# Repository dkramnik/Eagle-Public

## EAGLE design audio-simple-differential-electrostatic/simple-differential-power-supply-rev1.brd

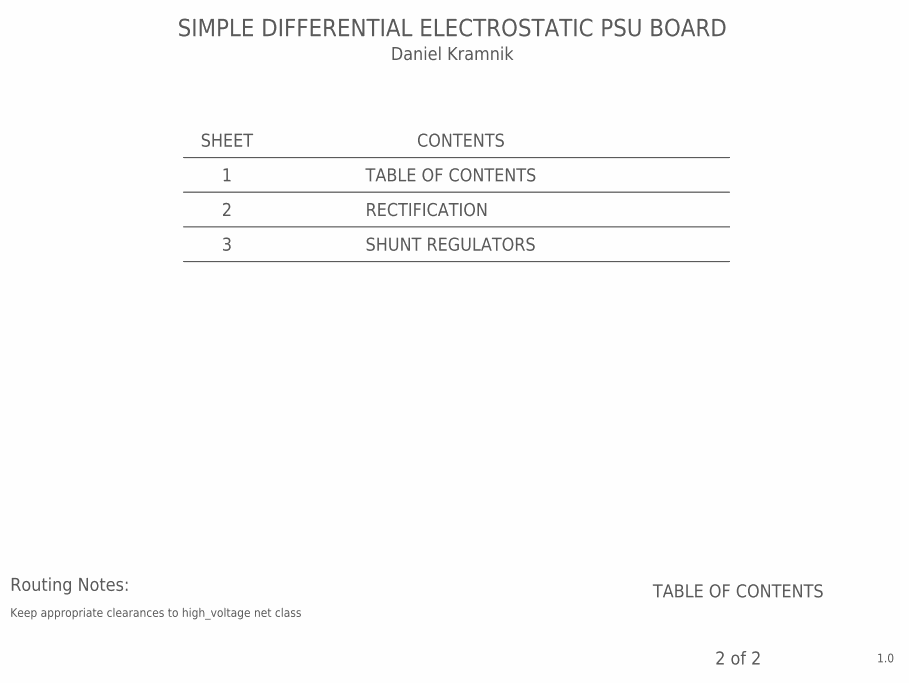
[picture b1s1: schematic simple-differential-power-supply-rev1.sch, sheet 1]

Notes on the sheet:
TABLE OF CONTENTS
1.0
2 of 2
SIMPLE DIFFERENTIAL ELECTROSTATIC PSU BOARD
SHEET
CONTENTS
Daniel Kramnik
RECTIFICATION
SHUNT REGULATORS
Routing Notes:
Keep appropriate clearances to high_voltage net class

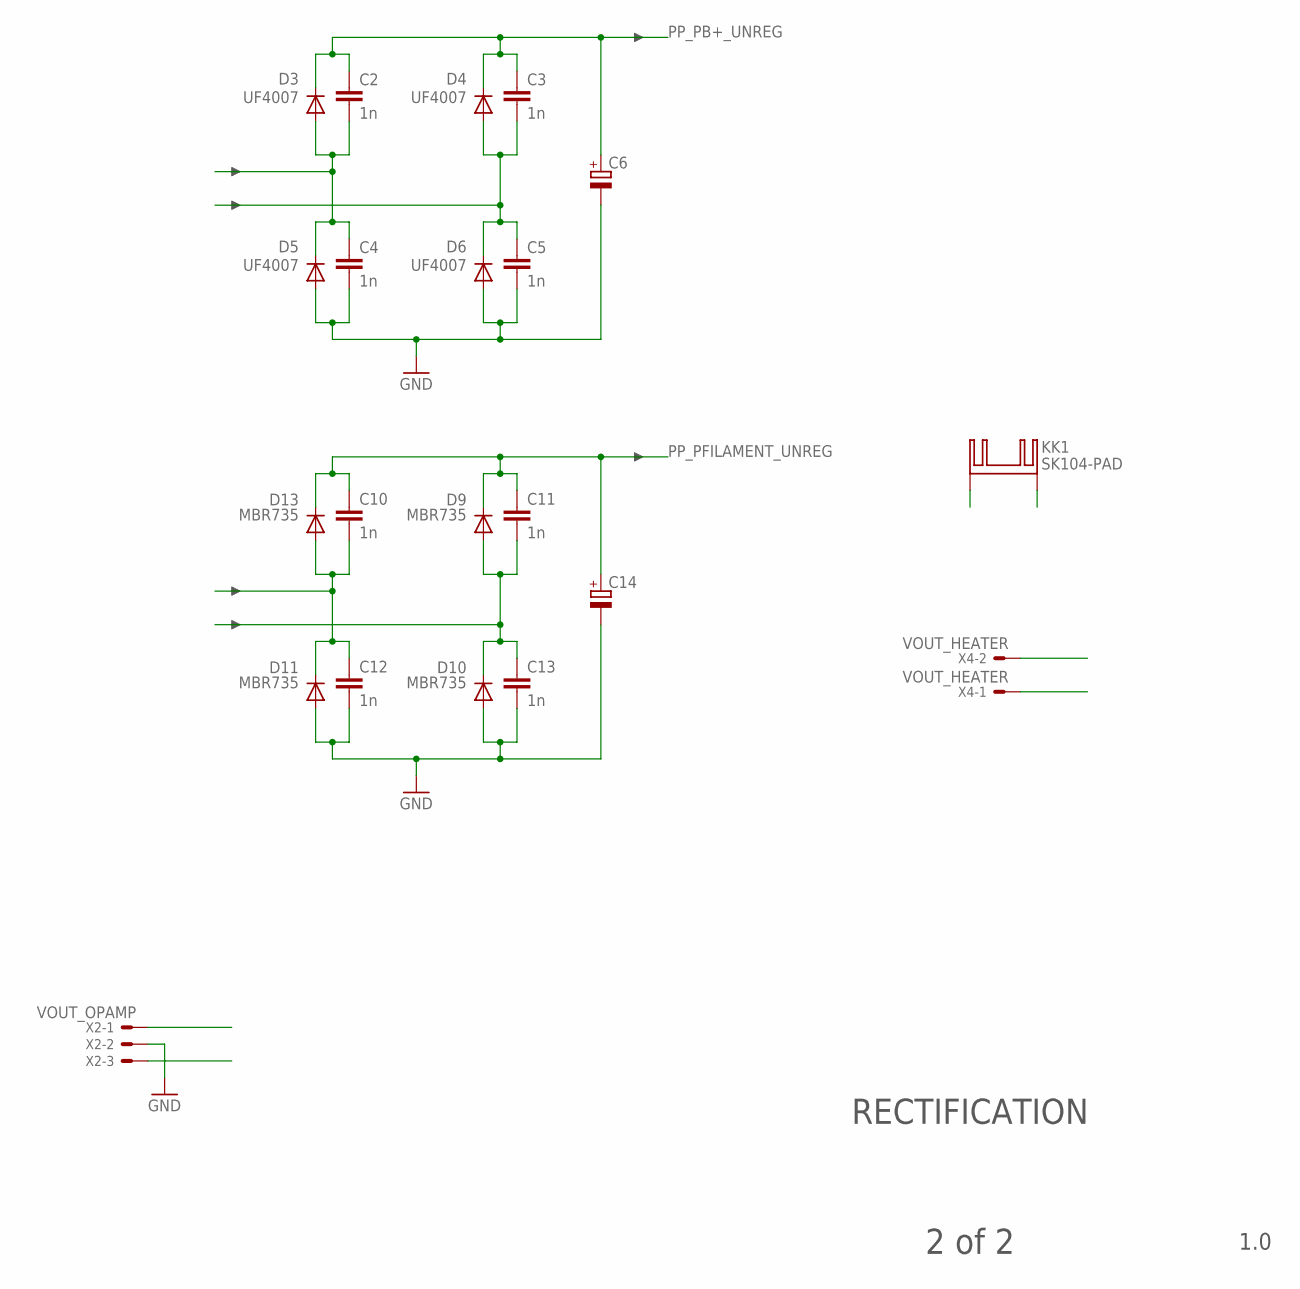
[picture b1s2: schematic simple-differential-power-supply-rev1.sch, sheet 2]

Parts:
C2, C3, C4, C5, C10, C11, C12, C13: 1n; C225-087X268
C6, C14: CPOL-EUE10-25; EB25D
D3, D4, D5, D6: UF4007; DO41-10
D9, D10, D11, D13: MBR735; TO220ACS
KK1: SK104-PAD
X2: VOUT_OPAMP; KK-156-3
X4: VOUT_HEATER; KK-156-2

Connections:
GND: C4.2, C5.2, C6.-, C12.2, C13.2, C14.-, D5.A, D6.A, D10.A, D11.A, X2.2; also elsewhere on the board
unnamed: C11.2, C13.1, D9.A, D10.C
unnamed: C10.2, C12.1, D11.C, D13.A
unnamed: C3.2, C5.1, D4.A, D6.C
unnamed: C2.2, C4.1, D3.A, D5.C
PP_PB+_UNREG: C2.1, C3.1, C6.+, D3.C, D4.C; also elsewhere on the board
PP_PFILAMENT_UNREG: C10.1, C11.1, C14.+, D9.C, D13.C

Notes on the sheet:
RECTIFICATION
1.0
2 of 2

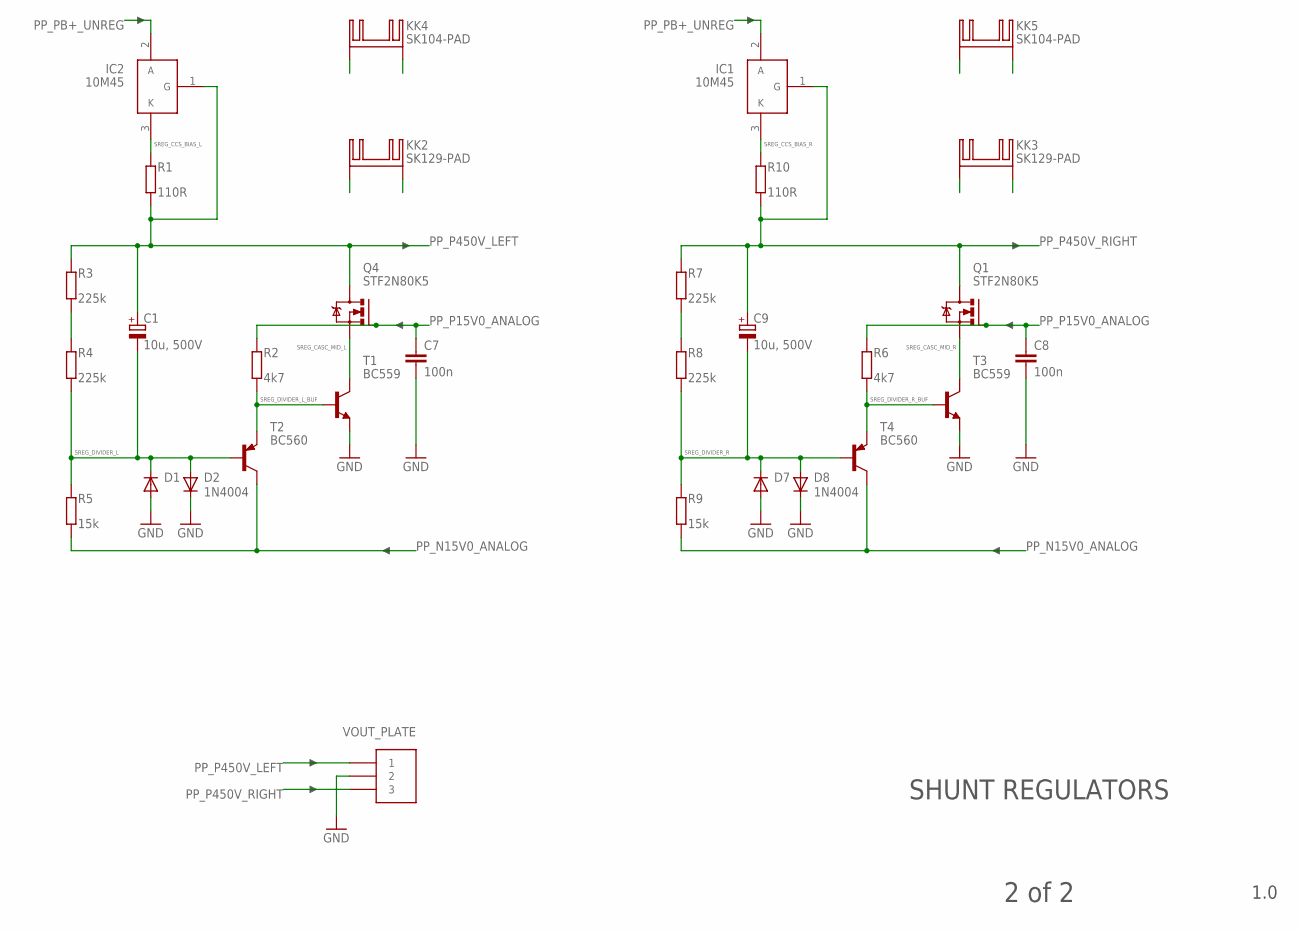
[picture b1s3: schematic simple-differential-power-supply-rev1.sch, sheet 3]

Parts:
C1, C9: 10u, 500V; EB25D
C7, C8: 100n; C050-025X075
D1, D2, D7, D8: 1N4004; DO41-10
IC1, IC2: 10M45; TO220V
J2: VOUT_PLATE; CONN_MOLEX_3PIN_MINI-FIT_JR
KK2, KK3: SK129-PAD; SK129
KK4, KK5: SK104-PAD
Q1, Q4: STF2N80K5; TO220BV
R1, R10: 110R; 0309/10
R2, R6: 4k7; 0309/10
R3, R4, R7, R8: 225k; 0309/10
R5, R9: 15k; 0309/10
T1, T3: BC559; TO92-EBC
T2, T4: BC560; TO92-EBC

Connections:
GND: C7.2, C8.2, D1.A, D2.C, D7.A, D8.C, J2.2, T1.E, T3.E; also elsewhere on the board
unnamed: R3.1, R4.2
unnamed: R7.1, R8.2
PP_N15V0_ANALOG: R5.1, R9.1, T2.C, T4.C
PP_P15V0_ANALOG: C7.1, C8.1, Q1.G, Q4.G, R2.2, R6.2
PP_P450V_LEFT: C1.+, IC2.1 (G), J2.1, Q4.D, R1.1, R3.2
PP_P450V_RIGHT: C9.+, IC1.1 (G), J2.3, Q1.D, R7.2, R10.1
PP_PB+_UNREG: IC1.2 (A), IC2.2 (A); also elsewhere on the board
SREG_CASC_MID_L: Q4.S, T1.C
SREG_CASC_MID_R: Q1.S, T3.C
SREG_CCS_BIAS_L: IC2.3 (K), R1.2
SREG_CCS_BIAS_R: IC1.3 (K), R10.2
SREG_DIVIDER_L: C1.-, D1.C, D2.A, R4.1, R5.2, T2.B
SREG_DIVIDER_L_BUF: R2.1, T1.B, T2.E
SREG_DIVIDER_R: C9.-, D7.C, D8.A, R8.1, R9.2, T4.B
SREG_DIVIDER_R_BUF: R6.1, T3.B, T4.E

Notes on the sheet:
SHUNT REGULATORS
1.0
2 of 2

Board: 2 copper layers, 52 parts (0 on the bottom side), 21 nets, no tracks yet.

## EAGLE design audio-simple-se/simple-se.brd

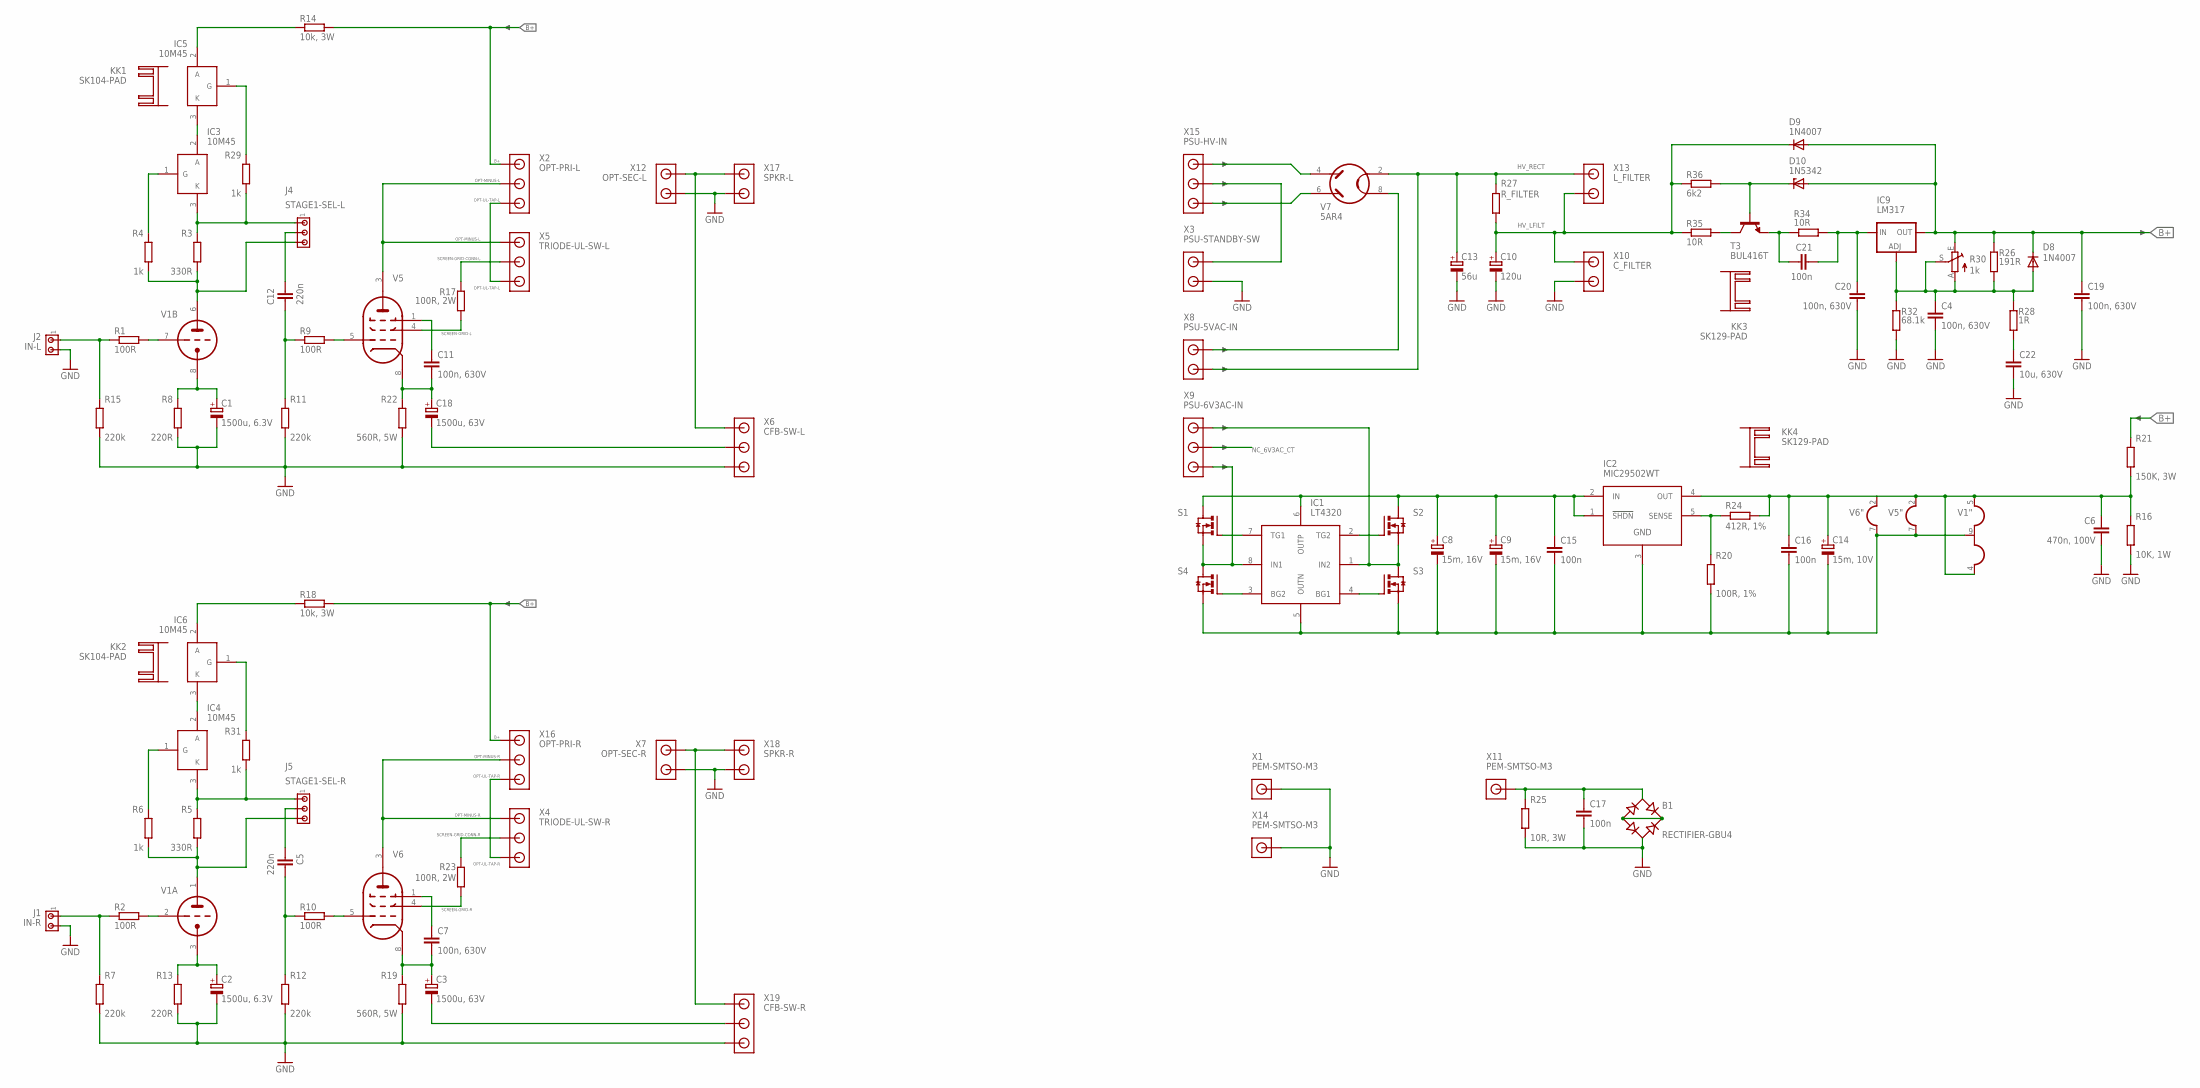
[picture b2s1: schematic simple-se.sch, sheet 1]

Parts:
B1: RECTIFIER-GBU4; GBU4
C1, C2: 1500u, 6.3V; E5-10,5
C3, C18: 1500u, 63V; E5-13
C4, C7, C11, C19, C20: 100n, 630V; C150-072X183
C5, C12: 220n; C275-113X316
C6: 470n, 100V; C075-063X106
C8, C9: 15m, 16V; E7,5-18
C10: 120u; EB30D
C13: 56u; EB22,5D
C14: 15m, 10V; E7,5-18
C15, C16: 100n; C050-055X075
C17: 100n; C102-043X133
C21: 100n; C150-072X183
C22: 10u, 630V; C150-072X183
D8, D9: 1N4007; DO41-10
D10: 1N5342; DO35Z10
IC1: LT4320; DIL08
IC2: MIC29502WT; TO220-5
IC3, IC4, IC5, IC6: 10M45; TO220V
IC9: LM317; 317TS
J1: IN-R; 1X2MTA
J2: IN-L; 1X2MTA
J4: STAGE1-SEL-L; 1X3MTA
J5: STAGE1-SEL-R; 1X3MTA
KK1, KK2: SK104-PAD
KK3, KK4: SK129-PAD; SK129
R1, R2, R9, R10: 100R; 0309/12
R3, R5: 330R; 0309/12
R4, R6, R29, R31: 1k; 0309/12
R7, R11, R12, R15: 220k; 0309/12
R8, R13: 220R; 0309/12
R14, R18: 10k, 3W; 0617/22
R16: 10K, 1W; 0309/12
R17, R23: 100R, 2W; 0411/12
R19, R22: 560R, 5W; 0922/22
R20: 100R, 1%; 0309/12
R21: 150K, 3W; 0617/22
R24: 412R, 1%; 0309/12
R25: 10R, 3W; 0617/17
R26: 191R; 0309/12
R27: R_FILTER; 0922/22
R28: 1R; 0309/12
R30: 1k; S64W
R32: 68.1k; 0309/12
R34, R35: 10R; 0309/12
R36: 6k2; 0309/12
S1, S2, S3, S4: MOSFET-N_DPAK; DPAK
T3: BUL416T; TO220V
V1: 12AT7-P; NOVAL
V5, V6: EL34-P; OKTAL
V7: 5AR4; OKTAL
X1, X11, X14: PEM-SMTSO-M3; SMTSO-M3
X2: OPT-PRI-L; MOLEX-SPOX-5281-3POS
X3: PSU-STANDBY-SW; MOLEX-SPOX-5281-2POS
X4: TRIODE-UL-SW-R; MOLEX-SPOX-5281-3POS
X5: TRIODE-UL-SW-L; MOLEX-SPOX-5281-3POS
X6: CFB-SW-L; MOLEX-SPOX-5281-3POS
X7: OPT-SEC-R; MOLEX-SPOX-5281-2POS
X8: PSU-5VAC-IN; MOLEX-SPOX-5281-2POS
X9: PSU-6V3AC-IN; MOLEX-SPOX-5281-3POS
X10: C_FILTER; MOLEX-SPOX-5281-2POS
X12: OPT-SEC-L; MOLEX-SPOX-5281-2POS
X13: L_FILTER; MOLEX-SPOX-5281-2POS
X15: PSU-HV-IN; MOLEX-SPOX-5281-3POS
X16: OPT-PRI-R; MOLEX-SPOX-5281-3POS
X17: SPKR-L; MOLEX-SPOX-5281-2POS
X18: SPKR-R; MOLEX-SPOX-5281-2POS
X19: CFB-SW-R; MOLEX-SPOX-5281-3POS

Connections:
B+: C19.1, D8.C, D9.A, D10.A, IC9.2 (OUT), R14.1, R18.1, R21.2, R26.2, R30.E, X2.P$1 (1), X16.P$1 (1)
GND: B1.AC2, C1.-, C2.-, C4.2, C6.2, C10.-, C13.-, C17.2, C19.2, C20.2, C22.2, J1.2, J2.2, R7.1, R8.1, R11.1, R12.1, R13.1, R15.1, R16.1, R19.1, R22.1, R25.1, R32.1, X1.P$1, X3.P$2 (2), X6.P$3 (3), X7.P$2 (2), X10.P$2 (2), X12.P$2 (2), X14.P$1, X17.P$2 (2), X18.P$2 (2), X19.P$3 (3)
HV_LFILT: C10.+, D9.C, R27.1, R35.2, R36.2, X10.P$1 (1), X13.P$2 (2)
HV_RECT: C13.+, R27.2, V7.2 (H1), X8.P$2 (2), X13.P$1 (1)
unnamed: R1.1, V1.7 (TG)
unnamed: J4.3, R3.1, R4.1, V1.6 (TA)
unnamed: R2.1, V1.2 (TG)
unnamed: J5.3, R5.1, R6.1, V1.1 (TA)
unnamed: IC4.3 (K), J5.1, R5.2, R31.1
unnamed: IC4.1 (G), R6.2
unnamed: IC3.3 (K), J4.1, R3.2, R29.1
unnamed: IC3.1 (G), R4.2
unnamed: J1.1, R2.2, R7.2
unnamed: J2.1, R1.2, R15.2
unnamed: R9.1, V5.5 (PG)
unnamed: B1.+, B1.-
unnamed: C5.2, R10.2, R12.2
unnamed: C12.1, R9.2, R11.2
unnamed: C1.+, R8.2, V1.8 (TK)
unnamed: C2.+, R13.2, V1.3 (TK)
unnamed: IC6.2 (A), R18.2
unnamed: IC3.2 (A), IC5.3 (K)
unnamed: C18.-, X6.P$2 (2)
unnamed: R10.1, V6.5 (PG)
unnamed: B1.AC1, C17.1, R25.2, X11.P$1
unnamed: X3.P$1 (1), X15.P$2 (2)
unnamed: X6.P$1 (1), X12.P$1 (1), X17.P$1 (1)
unnamed: R35.1, T3.2 (C)
unnamed: C4.1, D8.A, IC9.1 (ADJ), R26.1, R28.2, R30.A, R30.S, R32.2
unnamed: V7.4 (A1), X15.P$1 (1)
unnamed: IC1.7 (TG1), S1.1 (G)
unnamed: C21.1, R34.2, T3.3 (E)
unnamed: C20.1, C21.2, IC9.3 (IN), R34.1
unnamed: C11.2, C18.+, R22.2, V5.8 (PK)
unnamed: C7.1, V6.1 (PBG)
unnamed: C3.+, C7.2, R19.2, V6.8 (PK)
unnamed: V7.6 (A2), X15.P$3 (3)
unnamed: IC1.8 (IN1), S1.3 (S), S4.4 (D), X9.P$3 (3)
unnamed: V7.8 (H2), X8.P$1 (1)
unnamed: X7.P$1 (1), X18.P$1 (1), X19.P$1 (1)
unnamed: C22.1, R28.1
unnamed: C11.1, V5.1 (PBG)
unnamed: C8.+, C9.+, C15.1, IC1.6 (OUTP), IC2.1 (!SHDN), IC2.2 (IN), S1.4 (D), S2.4 (D)
unnamed: IC1.3 (BG2), S4.1 (G)
unnamed: IC1.2 (TG2), S2.1 (G)
unnamed: IC1.1 (IN2), S2.3 (S), S3.4 (D), X9.P$1 (1)
unnamed: IC1.4 (BG1), S3.1 (G)
unnamed: C8.-, C9.-, C14.-, C15.2, C16.2, IC1.5 (OUTN), IC2.3 (GND), R20.1, S3.3 (S), S4.3 (S), V1.9 (H2), V5.7 (H2), V6.7 (H2)
unnamed: C6.1, C14.+, C16.1, IC2.4 (OUT), R16.2, R21.1, R24.1, V1.4 (H1), V1.5 (H3), V5.2 (H1), V6.2 (H1)
unnamed: D10.C, R36.1, T3.1 (B)
unnamed: IC2.5 (SENSE), R20.2, R24.2
unnamed: IC5.1 (G), R29.2
unnamed: IC5.2 (A), R14.2
unnamed: C12.2, J4.2
unnamed: IC4.2 (A), IC6.3 (K)
unnamed: IC6.1 (G), R31.2
unnamed: C5.1, J5.2
NC_6V3AC_CT: X9.P$2 (2)
OPT-MINUS-L: V5.3 (PA), X2.P$2 (2), X5.P$1 (1)
OPT-MINUS-R: V6.3 (PA), X4.P$1 (1), X16.P$2 (2)
OPT-UL-TAP-L: X2.P$3 (3), X5.P$3 (3)
OPT-UL-TAP-R: X4.P$3 (3), X16.P$3 (3)
SCREEN-GRID-CONN-L: R17.1, X5.P$2 (2)
SCREEN-GRID-CONN-R: R23.1, X4.P$2 (2)
SCREEN-GRID-L: R17.2, V5.4 (PSG)
SCREEN-GRID-R: R23.2, V6.4 (PSG)

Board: 2 copper layers, 104 parts (9 on the bottom side), 65 nets, no tracks yet.

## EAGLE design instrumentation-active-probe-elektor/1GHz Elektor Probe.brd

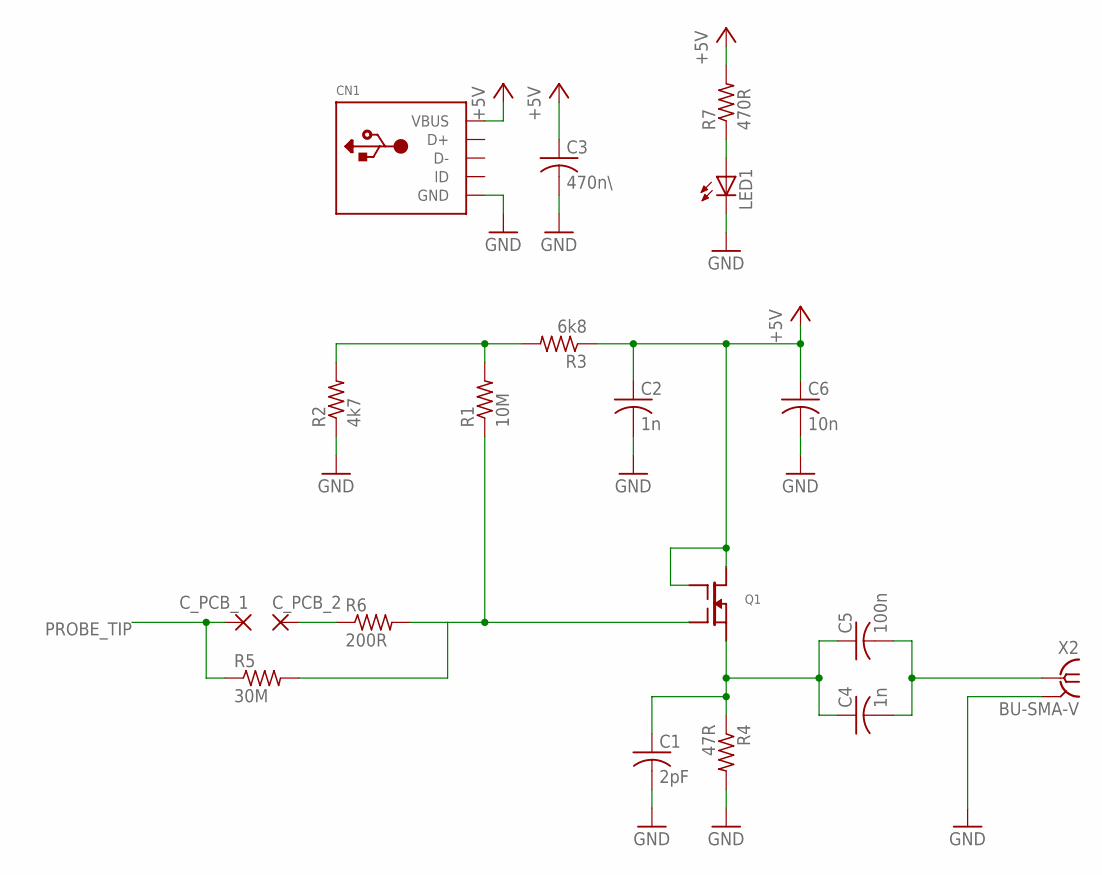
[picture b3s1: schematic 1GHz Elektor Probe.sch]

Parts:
C1: 2pF; C0805
C2, C4: 1n; C0805
C3: 470n\; C0805
C5: 100n; C0805
C6: 10n; C0805
CN1: USBMINIB; USB-MINIB
C_PCB_1, C_PCB_2: SMD5; SMD2,54-5,08
LED1: LED3MM
Q1: BF998; SOT143B
R1: 10M; R0805
R2: 4k7; R0805
R3: 6k8; R0805
R4: 47R; R0805
R5: 30M; R0805
R6: 200R; R0805
R7: 470R; R0805
X2: BU-SMA-V

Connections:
+5V: C2.1, C3.1, C6.1, CN1.VBUS, Q1.2 (D), Q1.3 (G2), R3.1, R7.2
GND: C1.2, C2.2, C3.2, C6.2, CN1.GND, LED1.K (C), R2.1, R4.2, X2.2 (GND), X2.3 (GND), X2.4 (GND), X2.5 (GND)
unnamed: C1.1, C4.1, C5.1, Q1.1 (S), R4.1
unnamed: C_PCB_2.1, R6.1
unnamed: R1.2, R2.2, R3.2
unnamed: LED1.A, R7.1
unnamed: C4.2, C5.2, X2.1
unnamed: Q1.4 (G1), R1.1, R5.2, R6.2
PROBE_TIP: C_PCB_1.1, R5.1

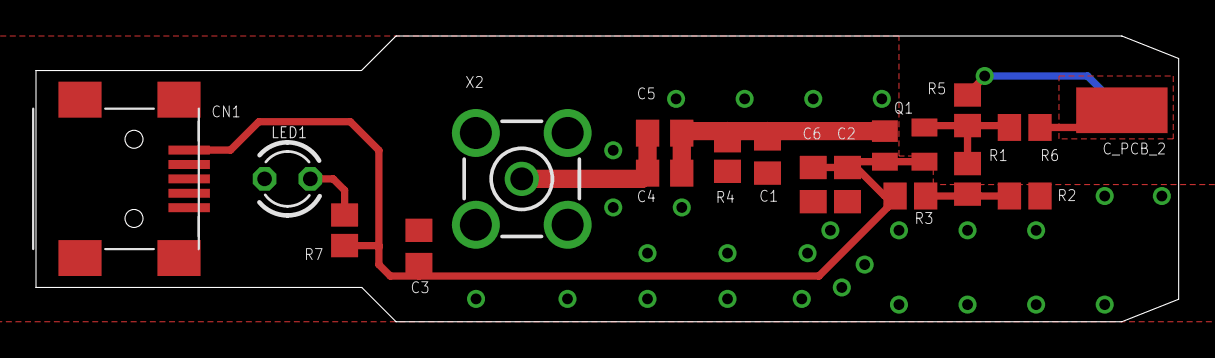
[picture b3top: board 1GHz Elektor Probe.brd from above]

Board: 2 copper layers, 63.5 x 15.9 mm, 19 parts (1 on the bottom side), 9 nets.

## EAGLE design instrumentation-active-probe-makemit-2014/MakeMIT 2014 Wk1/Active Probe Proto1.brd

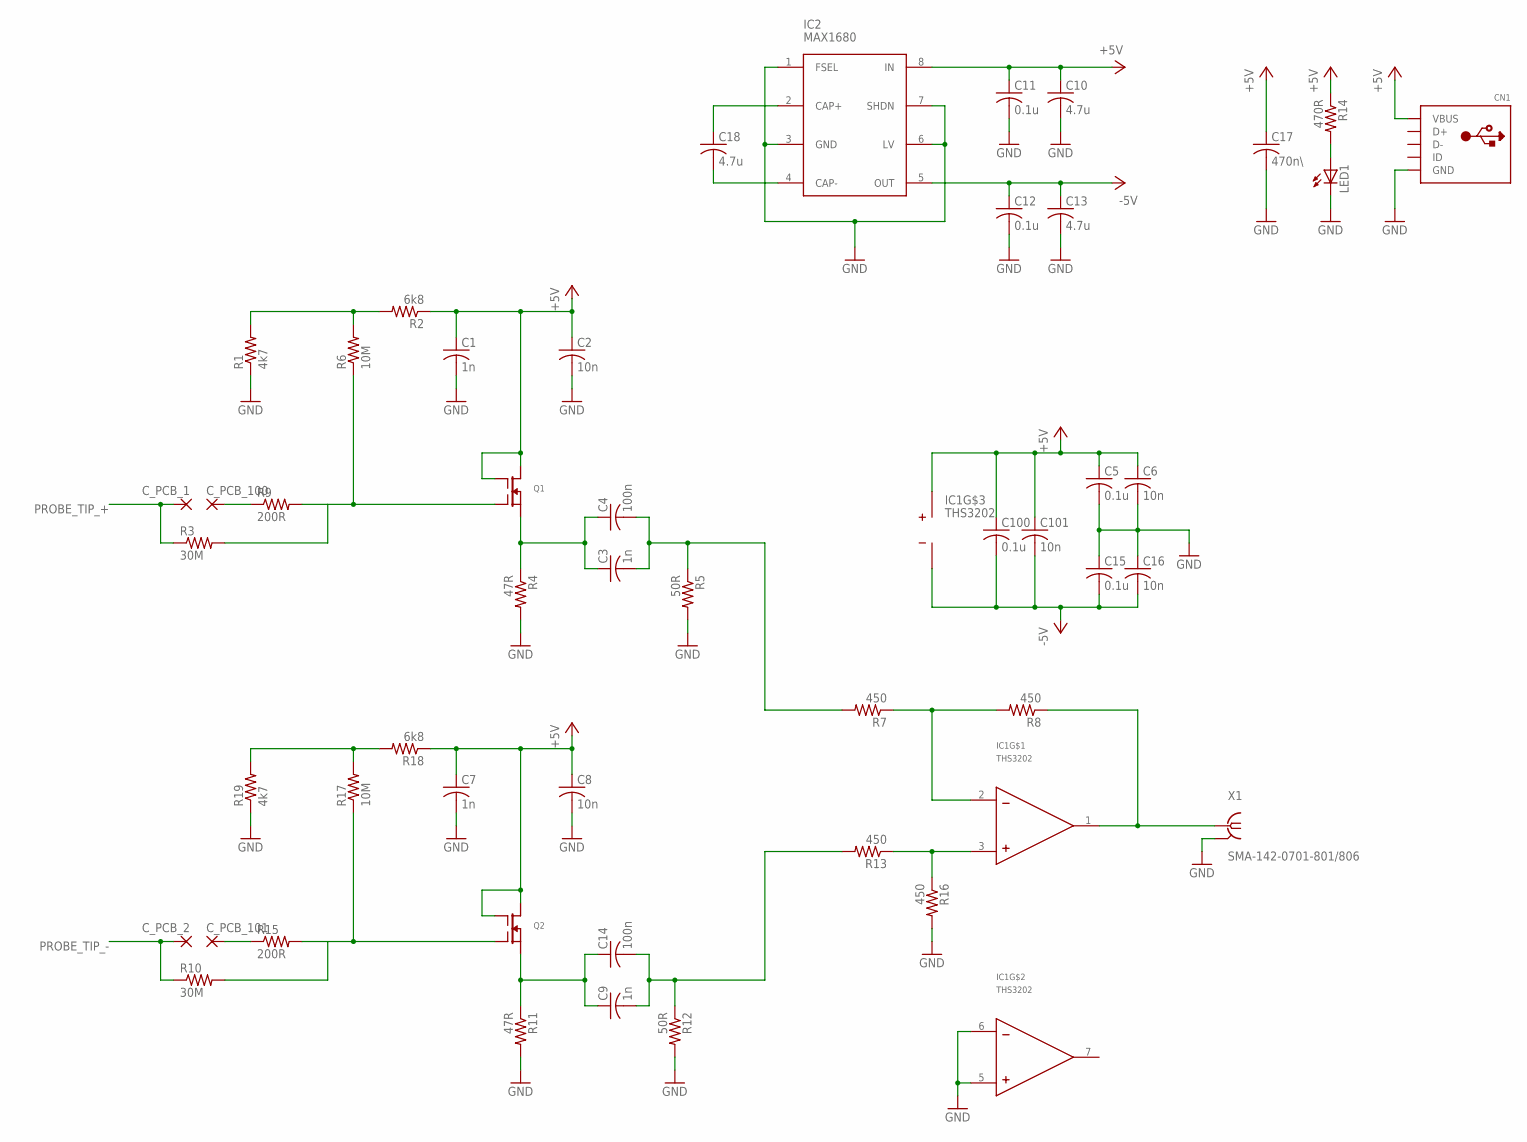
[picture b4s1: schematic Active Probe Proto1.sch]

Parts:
C1, C3, C7, C9: 1n; C0805
C2, C6, C8, C16, C101: 10n; C0805
C4, C14: 100n; C0805
C5, C11, C12, C15, C100: 0.1u; C0805
C10, C13, C18: 4.7u; C0805
C17: 470n\; C0805
CN1: USBMINIB; USB-MINIB
C_PCB_1, C_PCB_2, C_PCB_100, C_PCB_101: SMD5; SMD2,54-5,08
IC1: THS3202; SOIC8
IC2: MAX1680; SO8
LED1: LED3MM
Q1, Q2: BF998; SOT143B
R1, R19: 4k7; R0805
R2, R18: 6k8; R0805
R3, R10: 30M; R0805
R4, R11: 47R; R0805
R5, R12: 50R; R0805
R6, R17: 10M; R0805
R7, R8, R13, R16: 450; R0805
R9, R15: 200R; R0805
R14: 470R; R0805
X1: SMA-142-0701-801/806; J502-ND-142-0701-801/806

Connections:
+5V: C1.1, C2.1, C5.1, C6.1, C7.1, C8.1, C10.1, C11.1, C17.1, C100.1, C101.1, CN1.VBUS, IC1.8 (VCC), IC2.8 (IN), Q1.2 (D), Q1.3 (G2), Q2.2 (D), Q2.3 (G2), R2.1, R14.1, R18.1
-5V: C12.1, C13.1, C15.2, C16.2, C100.2, C101.2, IC1.4 (GND), IC2.5 (OUT)
GND: C1.2, C2.2, C5.2, C6.2, C7.2, C8.2, C10.2, C11.2, C12.2, C13.2, C15.1, C16.1, C17.2, CN1.GND, IC1.5 (IN+), IC1.6 (IN-), IC2.1 (FSEL), IC2.3 (GND), IC2.6 (LV), IC2.7 (SHDN), LED1.K (C), R1.1, R4.2, R5.2, R11.2, R12.2, R16.2, R19.1, X1.G@1 (GND), X1.G@2 (GND), X1.G@3 (GND), X1.G@4 (GND)
unnamed: R17.2, R18.2, R19.2
unnamed: C3.1, C4.1, Q1.1 (S), R4.1
unnamed: R1.2, R2.2, R6.2
unnamed: C_PCB_100.1, R9.1
unnamed: C3.2, C4.2, R5.1, R7.2
unnamed: Q1.4 (G1), R3.2, R6.1, R9.2
unnamed: C9.2, C14.2, R12.1, R13.2
unnamed: Q2.4 (G1), R10.2, R15.2, R17.1
unnamed: C9.1, C14.1, Q2.1 (S), R11.1
unnamed: C_PCB_101.1, R15.1
unnamed: LED1.A, R14.2
unnamed: IC1.1 (OUT), R8.1, X1.1
unnamed: C18.2, IC2.4 (CAP-)
unnamed: C18.1, IC2.2 (CAP+)
unnamed: IC1.3 (IN+), R13.1, R16.1
unnamed: IC1.2 (IN-), R7.1, R8.2
PROBE_TIP_+: C_PCB_1.1, R3.1
PROBE_TIP_-: C_PCB_2.1, R10.1

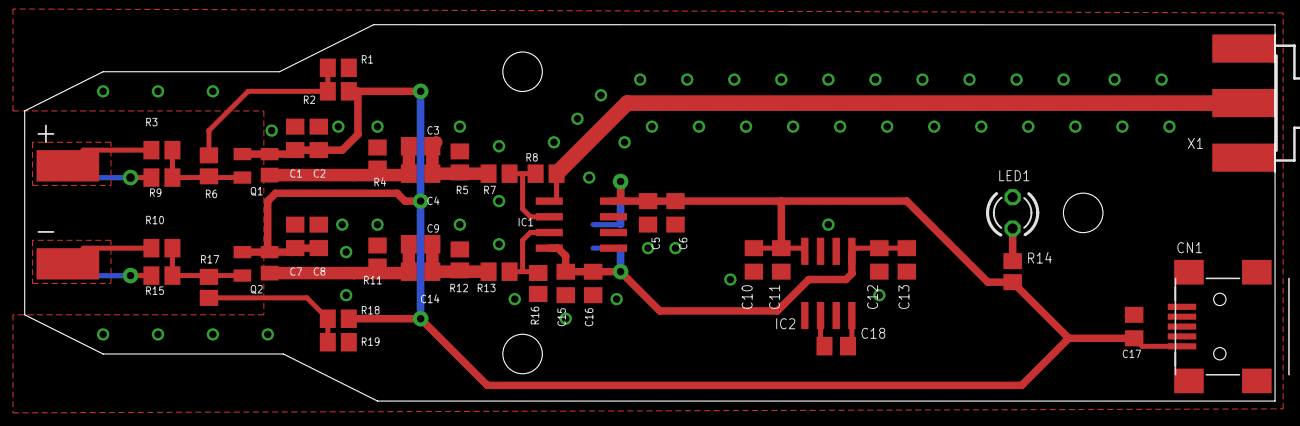
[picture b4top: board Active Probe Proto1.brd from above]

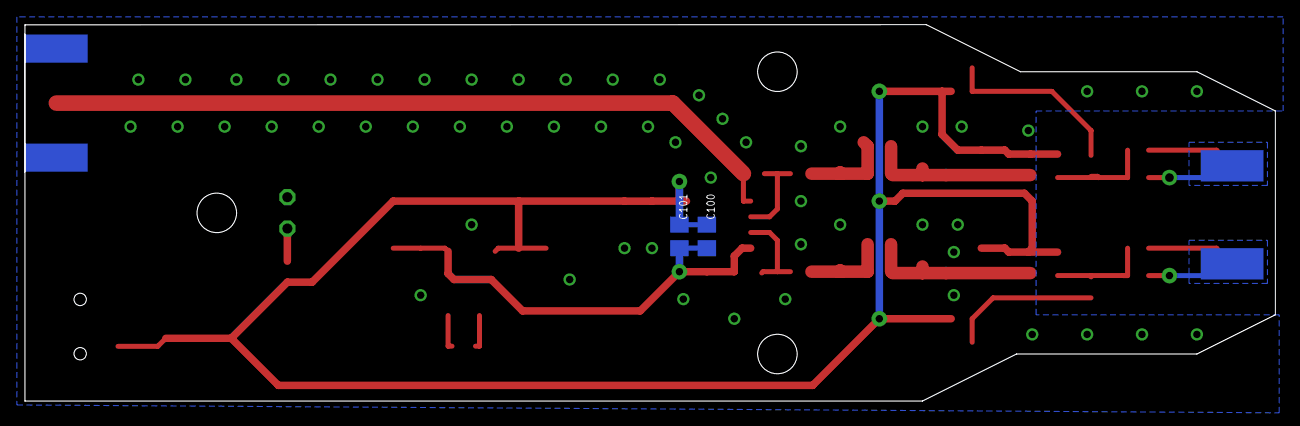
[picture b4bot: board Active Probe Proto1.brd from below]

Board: 2 copper layers, 101.3 x 30.5 mm, 50 parts (4 on the bottom side), 21 nets.

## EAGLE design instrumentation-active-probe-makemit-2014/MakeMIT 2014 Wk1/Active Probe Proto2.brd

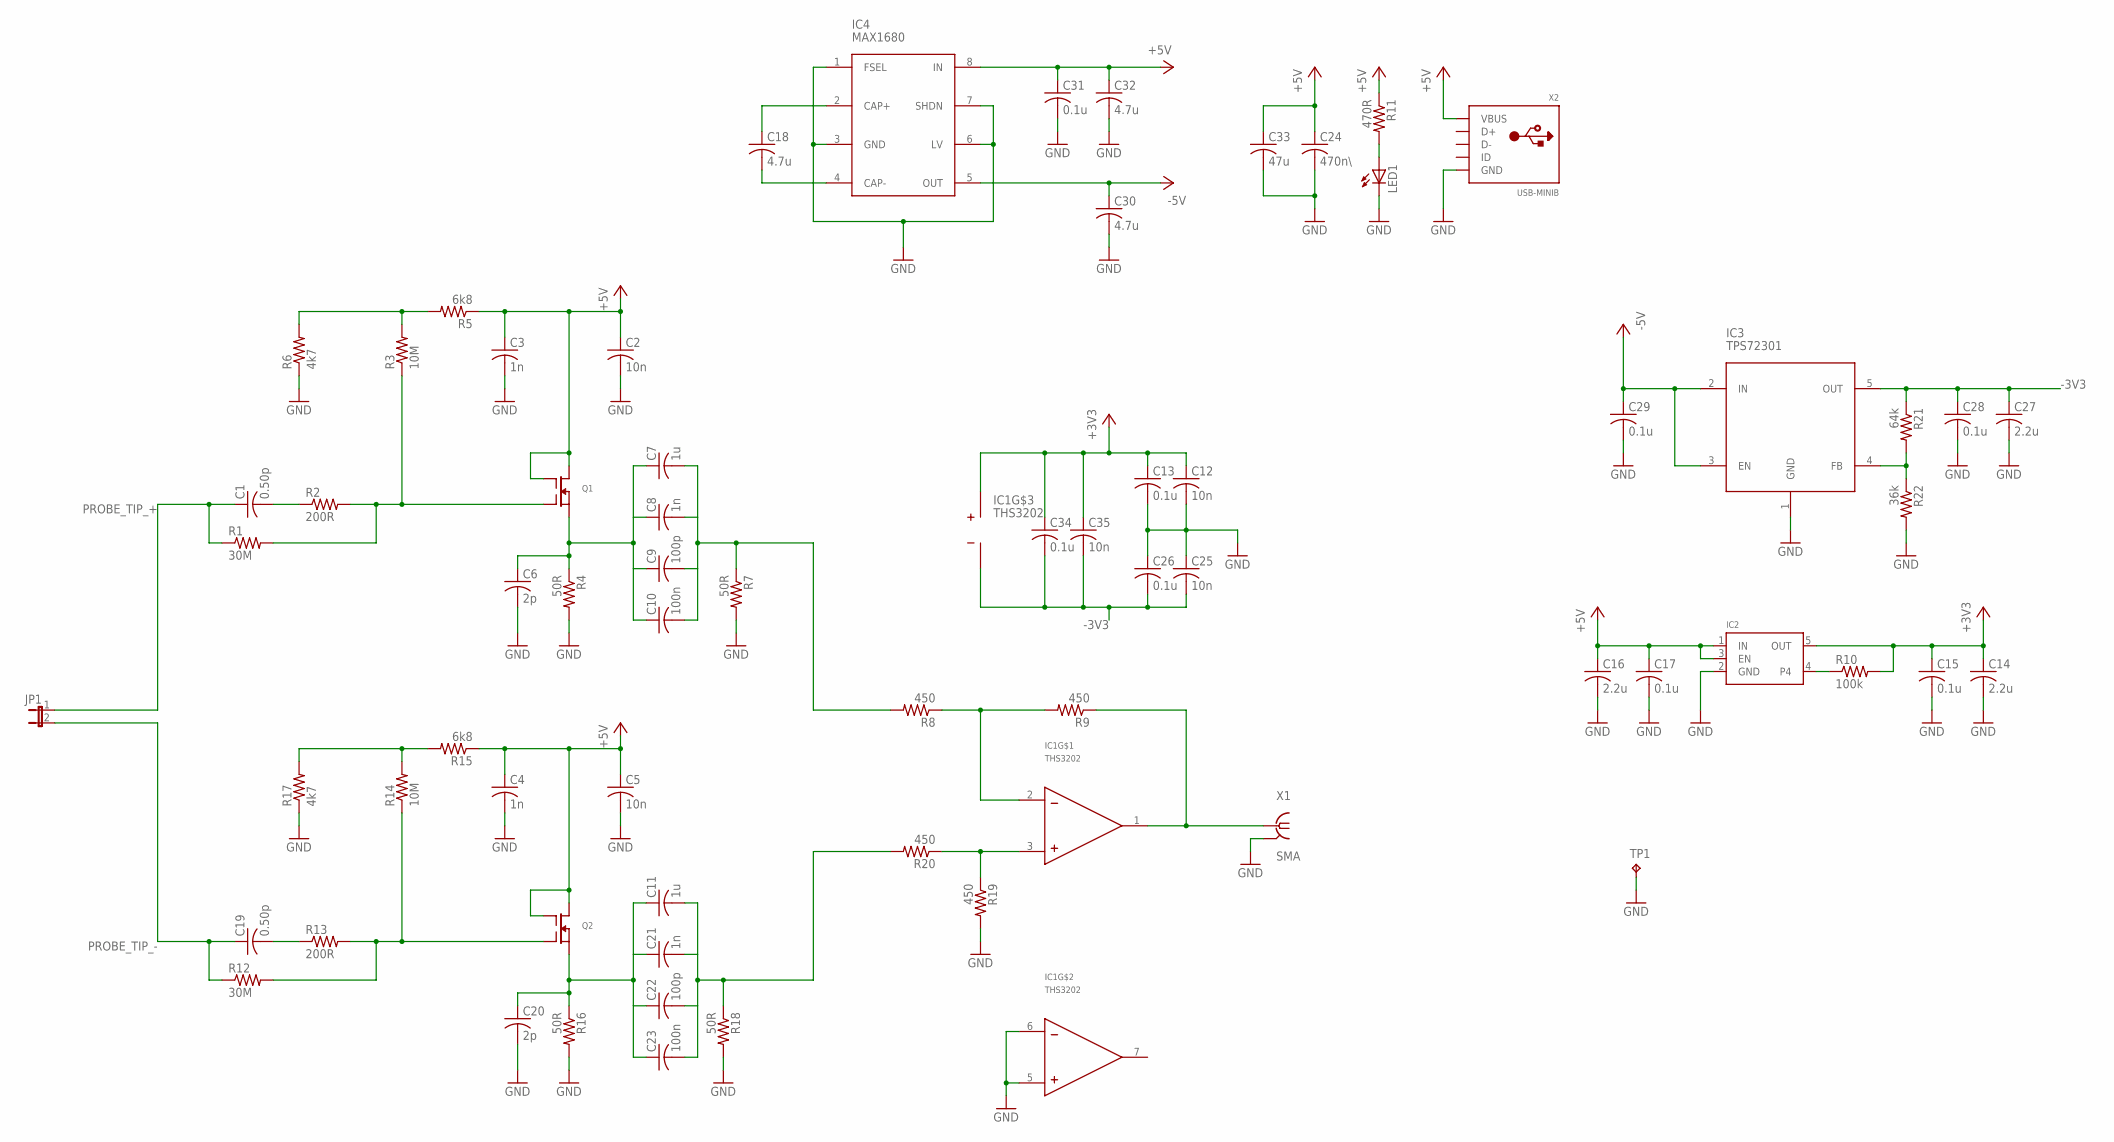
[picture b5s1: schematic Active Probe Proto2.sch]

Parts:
C1, C19: 0.50p; C0603
C2, C5, C12, C25, C35: 10n; C0603
C3, C4, C8, C21: 1n; C0603
C6, C20: 2p; C0603
C7, C11: 1u; C0603
C9, C22: 100p; C0603
C10, C23: 100n; C0603
C13, C15, C17, C26, C28, C29, C31, C34: 0.1u; C0603
C14, C16, C27: 2.2u; C0603
C18, C30, C32: 4.7u; C0603
C24: 470n\; C0603
C33: 47u; C1206
IC1: THS3202; SOIC8
IC2: VREG_SOT23-5; SOT23-5
IC3: TPS72301; SOT23-5L
IC4: MAX1680; SO8
JP1: HEADER_SIDE_2POS
LED1: LED3MM
Q1, Q2: BF998; SOT143B
R1, R12: 30M; R0603
R2, R13: 200R; R0603
R3, R14: 10M; R0603
R4, R7, R16, R18: 50R; R0603
R5, R15: 6k8; R0603
R6, R17: 4k7; R0603
R8, R9, R19, R20: 450; R0603
R10: 100k; R0603
R11: 470R; R0805
R21: 64k; R0603
R22: 36k; R0603
TP1: TPTP20SQ; TP20SQ
X1: SMA; J502-ND-142-0701-801/806
X2: USB-MINIB

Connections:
+3V3: C12.1, C13.1, C14.1, C15.1, C34.1, C35.1, IC1.8 (VCC), IC2.5 (OUT), R10.2
+5V: C2.1, C3.1, C4.1, C5.1, C16.1, C17.1, C24.1, C31.1, C32.1, C33.1, IC2.1 (IN), IC2.3 (EN), IC4.8 (IN), Q1.2 (D), Q1.3 (G2), Q2.2 (D), Q2.3 (G2), R5.1, R11.1, R15.1, X2.VBUS
-3V3: C25.2, C26.2, C27.1, C28.1, C34.2, C35.2, IC1.4 (GND), IC3.5 (OUT), R21.1
-5V: C29.1, C30.1, IC3.2 (IN), IC3.3 (EN), IC4.5 (OUT)
GND: C2.2, C3.2, C4.2, C5.2, C6.2, C12.2, C13.2, C14.2, C15.2, C16.2, C17.2, C20.2, C24.2, C25.1, C26.1, C27.2, C28.2, C29.2, C30.2, C31.2, C32.2, C33.2, IC1.5 (IN+), IC1.6 (IN-), IC2.2 (GND), IC3.1 (GND), IC4.1 (FSEL), IC4.3 (GND), IC4.6 (LV), IC4.7 (SHDN), LED1.K (C), R4.2, R6.1, R7.2, R16.2, R17.1, R18.2, R19.2, R22.2, TP1.TP, X1.G@1 (GND), X1.G@2 (GND), X1.G@3 (GND), X1.G@4 (GND), X2.GND
unnamed: R14.2, R15.2, R17.2
unnamed: C6.1, C7.1, C8.1, C9.1, C10.1, Q1.1 (S), R4.1
unnamed: R3.2, R5.2, R6.2
unnamed: IC2.4, R10.1
unnamed: C7.2, C8.2, C9.2, C10.2, R7.1, R8.2
unnamed: Q1.4 (G1), R1.2, R2.2, R3.1
unnamed: C11.2, C21.2, C22.2, C23.2, R18.1, R20.2
unnamed: Q2.4 (G1), R12.2, R13.2, R14.1
unnamed: C11.1, C20.1, C21.1, C22.1, C23.1, Q2.1 (S), R16.1
unnamed: LED1.A, R11.2
unnamed: C19.2, R13.1
unnamed: IC1.1 (OUT), R9.1, X1.1
unnamed: C18.2, IC4.4 (CAP-)
unnamed: C18.1, IC4.2 (CAP+)
unnamed: IC1.3 (IN+), R19.1, R20.1
unnamed: IC1.2 (IN-), R8.1, R9.2
unnamed: C1.2, R2.1
unnamed: IC3.4 (FB), R21.2, R22.1
PROBE_TIP_+: C1.1, JP1.1, R1.1
PROBE_TIP_-: C19.1, JP1.2, R12.1

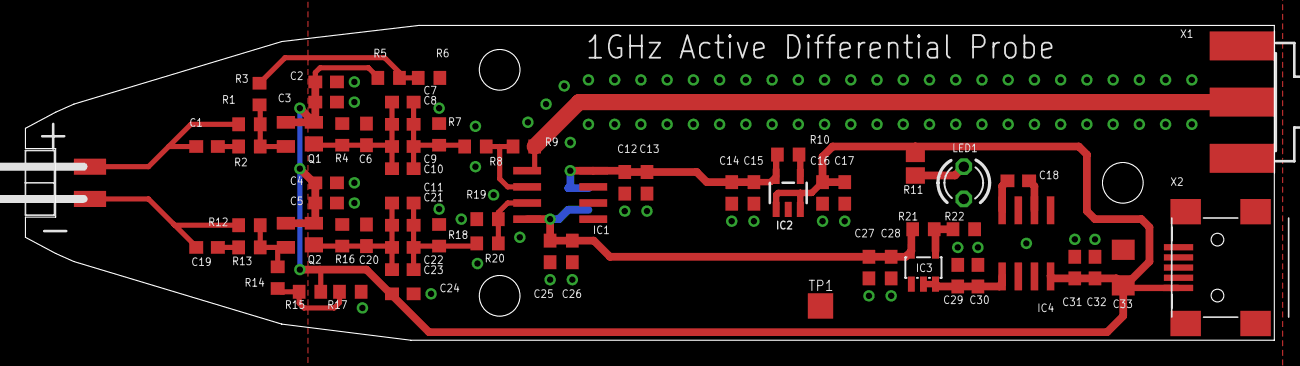
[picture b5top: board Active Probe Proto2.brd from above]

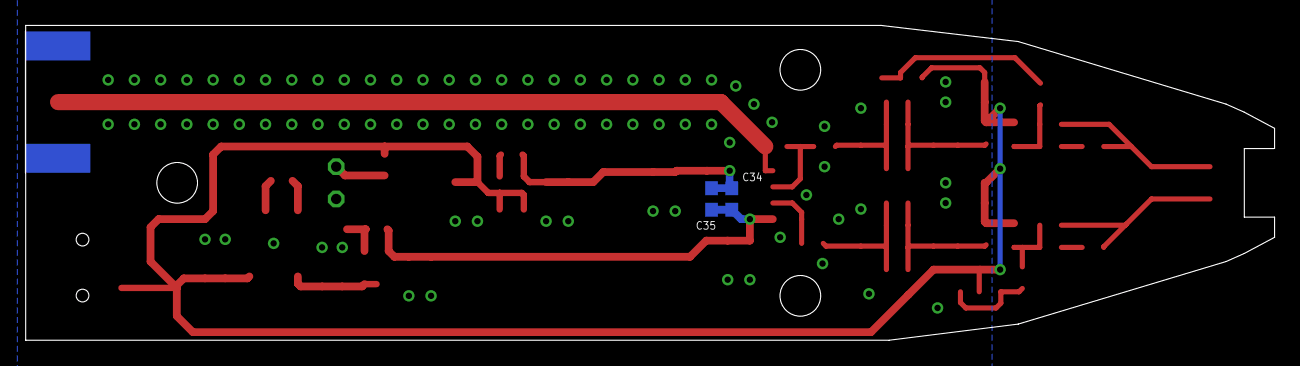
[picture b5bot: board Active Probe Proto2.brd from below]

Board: 2 copper layers, 98.3 x 24.8 mm, 68 parts (2 on the bottom side), 25 nets.

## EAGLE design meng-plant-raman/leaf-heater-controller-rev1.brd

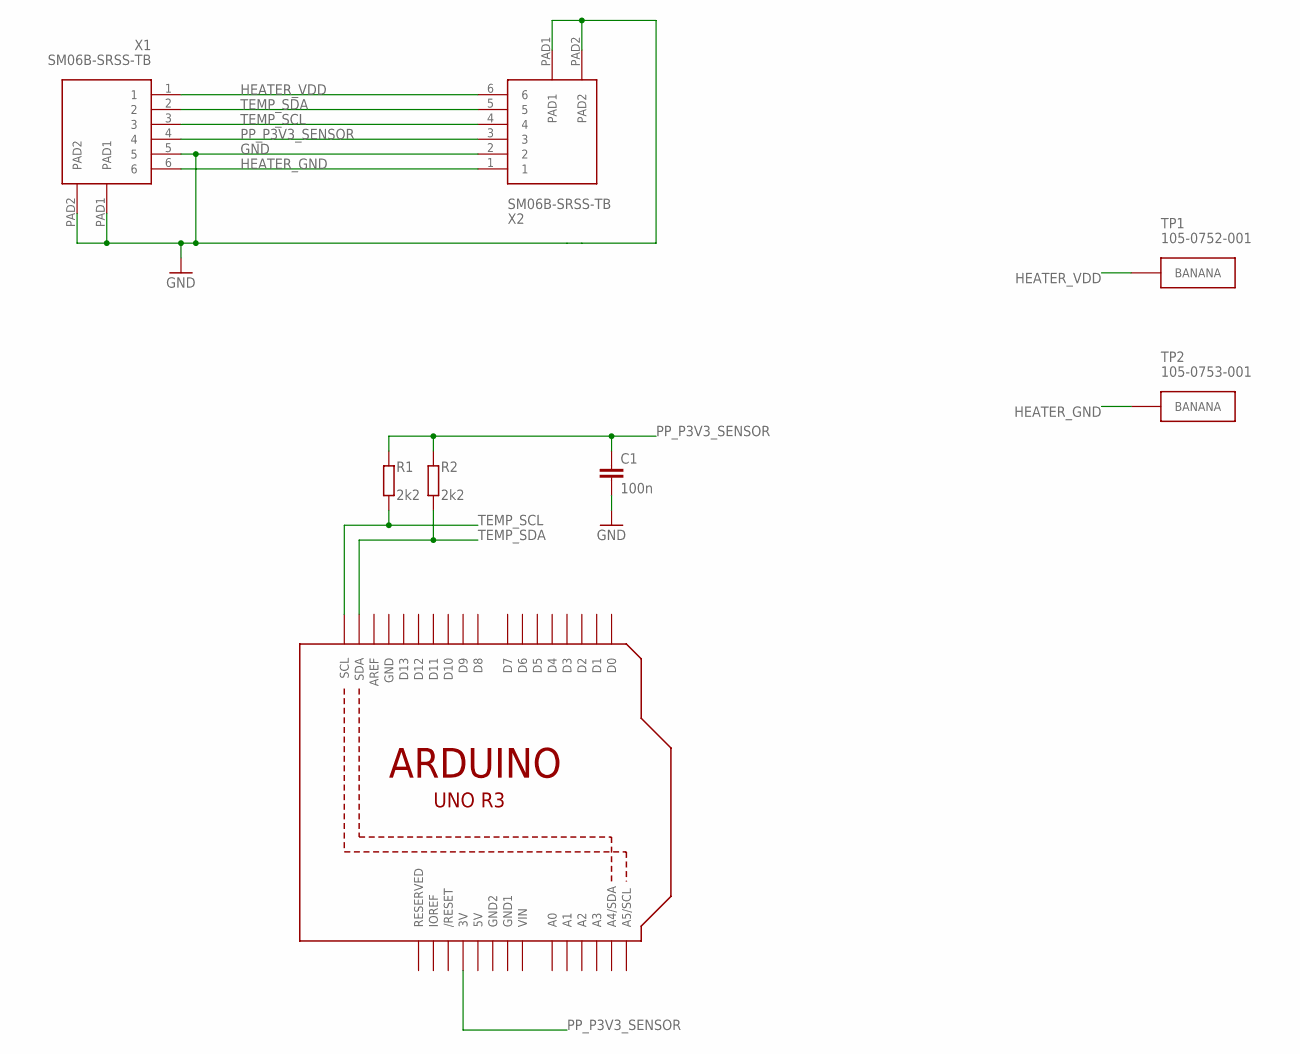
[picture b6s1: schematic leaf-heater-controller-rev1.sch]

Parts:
C1: 100n; C0603
R1, R2: 2k2; R0603
TP1: 105-0752-001; CINCH-BANANA-105-075X-001
TP2: 105-0753-001; CINCH-BANANA-105-075X-001
U1: ARDUINOR3-DIMENSION; ARDUINOR3
X1, X2: SM06B-SRSS-TB; JST-SM06B-SRSS-TB

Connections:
5V: U1.5V
GND: C1.2, U1.GND, X1.5, X1.PAD1, X1.PAD2, X2.2, X2.PAD1, X2.PAD2
GND1: U1.GND1
GND2: U1.GND2
HEATER_GND: TP2.1, TP2.2, X1.6, X2.1
HEATER_VDD: TP1.1, TP1.2, X1.1, X2.6
PP_P3V3_SENSOR: C1.1, R1.2, R2.2, U1.3V, X1.4, X2.3
TEMP_SCL: R1.1, U1.SCL, X1.3, X2.4
TEMP_SDA: R2.1, U1.SDA, X1.2, X2.5
VIN: U1.VIN

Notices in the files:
parts and their libraries:
microbuilder: This work is placed in the public domain, and may be freely used for commercial and non-commercial work with the following conditions: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
